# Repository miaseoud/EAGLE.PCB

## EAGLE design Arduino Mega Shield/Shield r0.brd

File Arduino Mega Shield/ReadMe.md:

# Arduino Mega Shield IRC'15 autonomous robot
The organization of shield is based on the needs 
of each connected device: (PWM, Servo, Analog,....)
+ the order of pins to use uni-directional cables

## Arduino Mega Shield autonomous robot supporting:
* 2x QTR 8 IR Analog sensor array
* 4x Servo Motors, signal supplied from Arduino and power supplied exnternally
* 1x ULN293 Motor Driver (PWM)
* 1x Motor Driver Module (PWM)
* 4x Digital Light Finder sensors
* 4x Digital IR sensors
* 3x Ultrasonic sensors

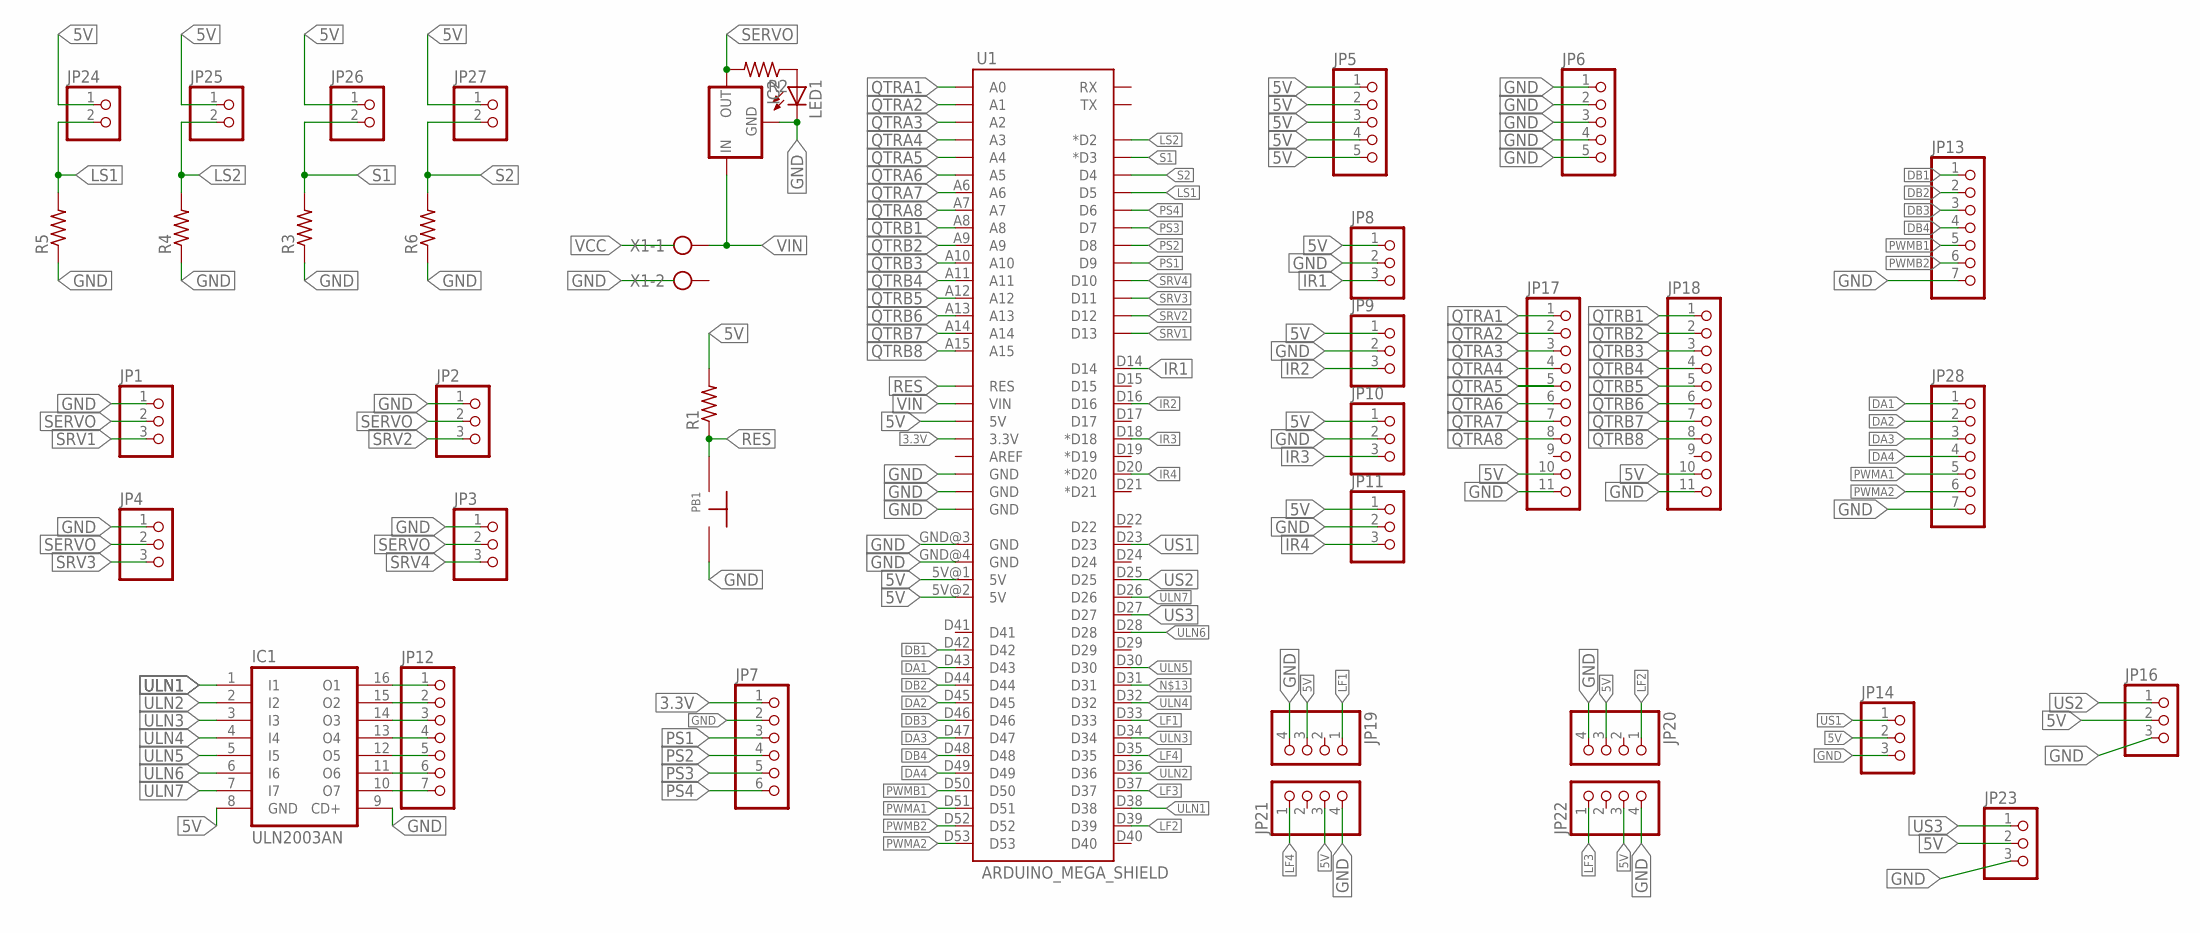
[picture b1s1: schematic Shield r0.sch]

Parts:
IC1: ULN2003AN; DIL16
IC2: 78XXS
JP1, JP2, JP3, JP4, JP8, JP9, JP10, JP11, JP14, JP16, JP23: PINHD-1X3; 1X03
JP5, JP6: PINHD-1X5; 1X05
JP7: PINHD-1X6; 1X06
JP12, JP13, JP28: PINHD-1X7; 1X07
JP17, JP18: PINHD-1X11; 1X11
JP19, JP20, JP21, JP22: PINHD-1X4; 1X04
JP24, JP25, JP26, JP27: PINHD-1X2; 1X02
LED1: LED5MM
PB1: PUSH; PUSHBUTTON
R1, R2, R3, R4, R5, R6: R-US_0207/10; 0207/10
U1: ARDUINO_MEGA_SHIELD
X1: AK500/2-H

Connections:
3.3V: JP7.1, U1.3.3V
5V: IC1.8 (GND), JP5.1, JP5.2, JP5.3, JP5.4, JP5.5, JP8.1, JP9.1, JP10.1, JP11.1, JP14.2, JP16.2, JP17.10, JP18.10, JP19.3, JP20.3, JP21.3, JP22.3, JP23.2, JP24.1, JP25.1, JP26.1, JP27.1, R1.2, U1.5V@0 (5V), U1.5V@1 (5V), U1.5V@2 (5V)
DA1: JP28.1, U1.D43
DA2: JP28.2, U1.D45
DA3: JP28.3, U1.D47
DA4: JP28.4, U1.D49
DB1: JP13.1, U1.D42
DB2: JP13.2, U1.D44
DB3: JP13.3, U1.D46
DB4: JP13.4, U1.D48
GND: IC1.9 (CD+), IC2.GND, JP1.1, JP2.1, JP3.1, JP4.1, JP6.1, JP6.2, JP6.3, JP6.4, JP6.5, JP7.2, JP8.2, JP9.2, JP10.2, JP11.2, JP13.7, JP14.3, JP16.3, JP17.11, JP18.11, JP19.4, JP20.4, JP21.4, JP22.4, JP23.3, JP28.7, LED1.K (C), PB1.P$2 (3), R3.1, R4.1, R5.1, R6.1, U1.GND@0 (GND), U1.GND@1 (GND), U1.GND@2 (GND), U1.GND@3 (GND), U1.GND@4 (GND)
IR1: JP8.3, U1.D14
IR2: JP9.3, U1.D16
IR3: JP10.3, U1.D18 (*D18)
IR4: JP11.3, U1.D20 (*D20)
LF1: JP19.1, U1.D33
LF2: JP20.1, U1.D39
LF3: JP22.1, U1.D37
LF4: JP21.1, U1.D35
LS1: JP24.2, R5.2, U1.D5
LS2: JP25.2, R4.2, U1.D2 (*D2)
unnamed: LED1.A, R2.1
unnamed: IC1.16 (O1), JP12.1
unnamed: IC1.15 (O2), JP12.2
unnamed: IC1.14 (O3), JP12.3
unnamed: IC1.13 (O4), JP12.4
unnamed: IC1.12 (O5), JP12.5
unnamed: IC1.11 (O6), JP12.6
unnamed: IC1.10 (O7), JP12.7
PS1: JP7.3, U1.D9
PS2: JP7.4, U1.D8
PS3: JP7.5, U1.D7
PS4: JP7.6, U1.D6
PWMA1: JP28.5, U1.D51
PWMA2: JP28.6, U1.D53
PWMB1: JP13.5, U1.D50
PWMB2: JP13.6, U1.D52
QTRA1: JP17.1, U1.A0
QTRA2: JP17.2, U1.A1
QTRA3: JP17.3, U1.A2
QTRA4: JP17.4, U1.A3
QTRA5: JP17.5, U1.A4
QTRA6: JP17.6, U1.A5
QTRA7: JP17.7, U1.A6
QTRA8: JP17.8, U1.A7
QTRB1: JP18.1, U1.A8
QTRB2: JP18.2, U1.A9
QTRB3: JP18.3, U1.A10
QTRB4: JP18.4, U1.A11
QTRB5: JP18.5, U1.A12
QTRB6: JP18.6, U1.A13
QTRB7: JP18.7, U1.A14
QTRB8: JP18.8, U1.A15
RES: PB1.P$1 (2), R1.1, U1.RES
S1: JP26.2, R3.2, U1.D3 (*D3)
S2: JP27.2, R6.2, U1.D4
SERVO: IC2.OUT, JP1.2, JP2.2, JP3.2, JP4.2, R2.2
SRV1: JP1.3, U1.D13
SRV2: JP2.3, U1.D12
SRV3: JP4.3, U1.D11
SRV4: JP3.3, U1.D10
ULN1: IC1.1 (I1), U1.D38
ULN2: IC1.2 (I2), U1.D36
ULN3: IC1.3 (I3), U1.D34
ULN4: IC1.4 (I4), U1.D32
ULN5: IC1.5 (I5), U1.D30
ULN6: IC1.6 (I6), U1.D28
ULN7: IC1.7 (I7), U1.D26
US1: JP14.1, U1.D23
US2: JP16.1, U1.D25
US3: JP23.1, U1.D27
VIN: IC2.IN, U1.VIN, X1.1

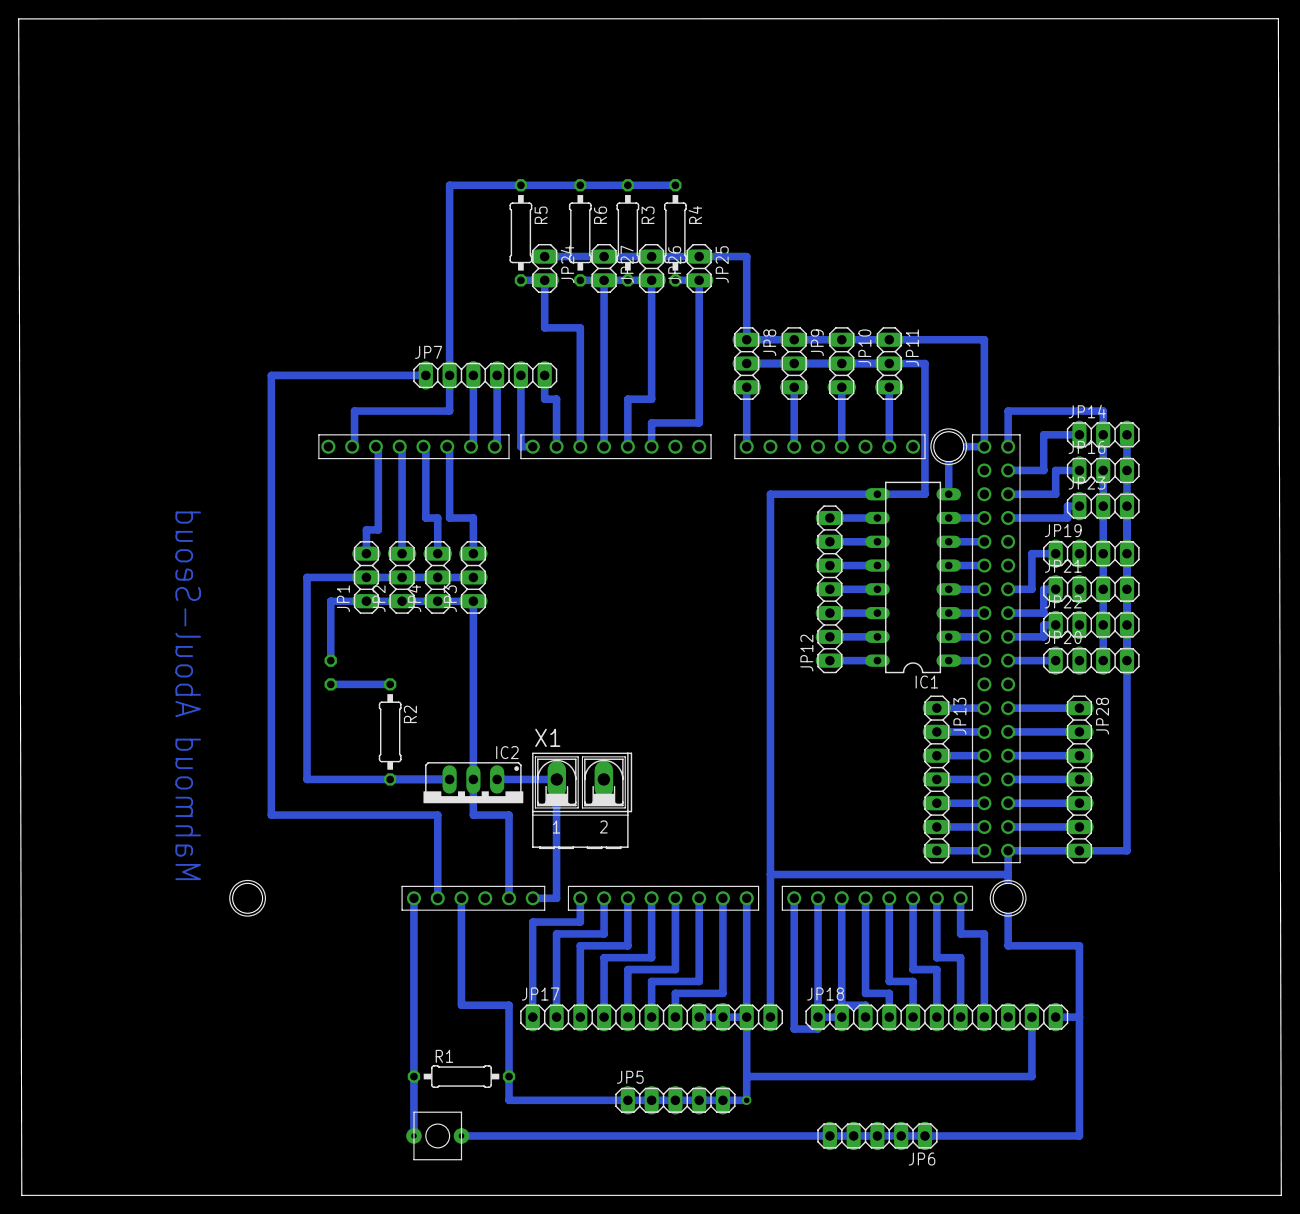
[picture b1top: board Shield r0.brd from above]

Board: 2 copper layers, 134.9 x 125.8 mm, 39 parts (1 on the bottom side), 72 nets.

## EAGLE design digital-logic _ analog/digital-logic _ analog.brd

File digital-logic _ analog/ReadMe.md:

# Off-shelf components robot
PCB for robot moving thorugh a maze using sensor,
but without the use of any microcontroller. Just relying 
on truth tables driving input for ULN293 motor driver.

IC connected on board:
Digital logic ICs: AND, OR, NOT
2x Op-amps
1x Counter 74190
1x MUX 74157
1x Timer IC 555
1x ULN293 motor driver
LEDs and Switches
2x digital sensors
1x analog sensor

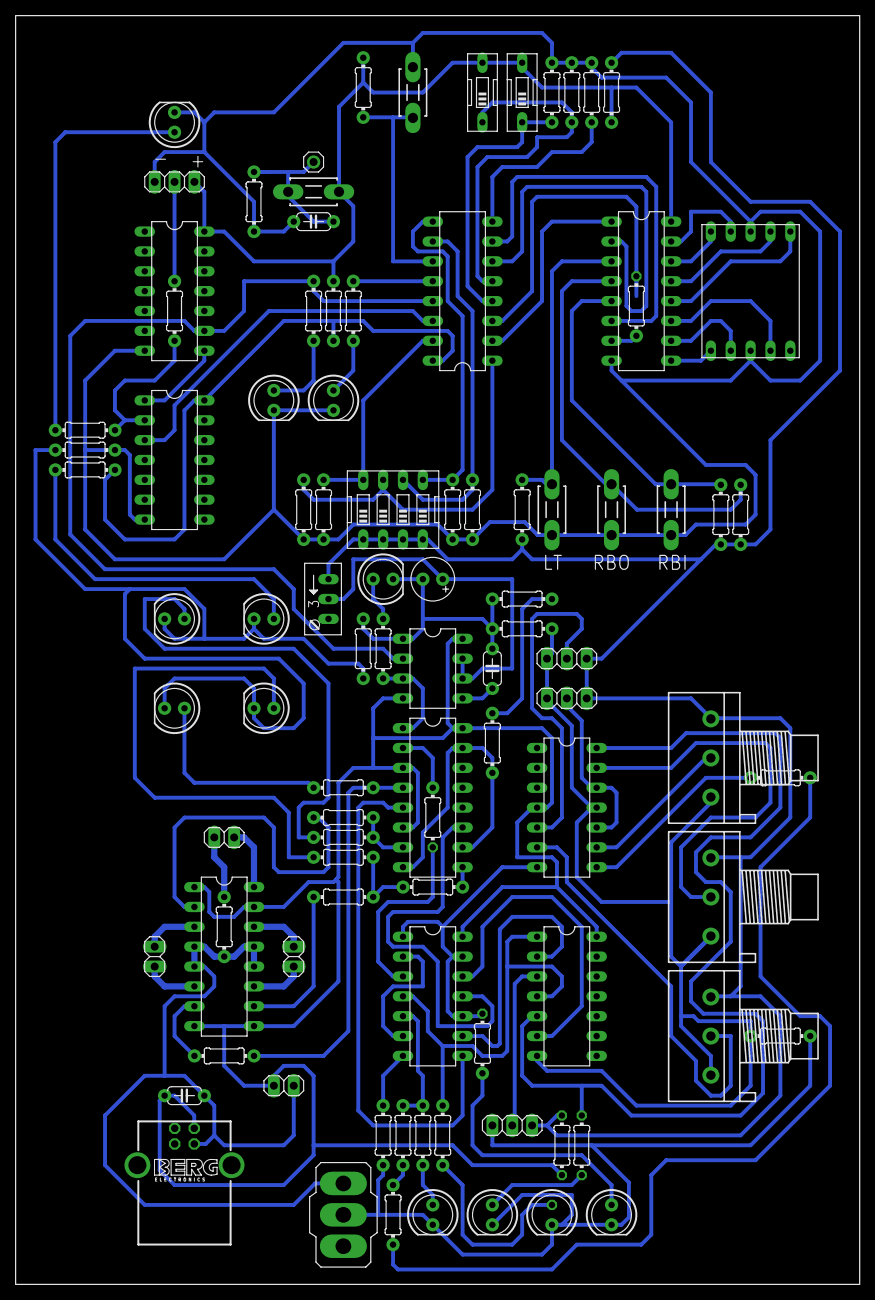
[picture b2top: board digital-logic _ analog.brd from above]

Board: 2 copper layers, 107.9 x 162.2 mm, 95 parts (0 on the bottom side), 68 nets.

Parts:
BLACK: 1X03
C1: 10nF; C050-024X044
C2, C3: 100nF; C050-024X044
C4: 1uF; E2,5-6
DIS1: HD-H103; HDSP-M
FLAME: 1X03
IC1: L293D; DIL16
IC2: LM324N; DIL14
IC3, IC9: 74LS32N; DIL14
IC4: 74ALS04N; DIL14
IC5: 74LS157N; DIL16
IC6: 74190N; DIL16
IC7: NE555; DIL-08
IC8: 74LS48N; DIL16
IC10: 74LS04N; DIL14
IR: 1X03
JP2, JP3, JP4, JP5: 1X02
JP7: 1X01
LED1, LED2, LED3, LED4, LED5, LED6, LED7, LED8, LED9, LED10, LED11, LED12: LED5MM
R1, R2, R3: 3RP/1610N
R4, R5, R6, R7, R8, R9, R10, R11, R13, R14, R15, R16, R17, R18, R19, R20, R21, R22, R23, R24, R25, R26, R49: 0204/7
R27, R28, R29, R30, R31, R32, R33, R34, R35, R36, R37, R38, R39, R40, R41, R42, R43, R44, R45, R46, R47, R48: 0; 0204/7
R50: RJ9W
S1: 320-916
S5: DTS-3; DTS-3@1
SHARP: 1X03
SW1: EDG-04
SW2, SW3, SW4, SW7: DTS-3; DTS-3@1
SW5, SW6: EDG-01
X1: PN61729-S

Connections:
BLACK: BLACK.2, IC9.2, R13.2, R36.1, R36.2
CLK: IC6.14, IC9.3
DIS: C4.+, IC7.6, IC7.7, R50.S
FLAME: IC2.7, IC3.1, IC3.10, IC3.13, R11.2
FRONT: IC3.4, IC4.1, IC4.4, R10.2
FRONT': IC4.3, IR.2
GND: BLACK.1, C1.2, C2.1, C3.2, C4.-, DIS1.3, DIS1.8, FLAME.1, IC1.4, IC1.5, IC1.12, IC1.13, IC2.11, IC3.7, IC4.7, IC5.8, IC5.10, IC5.15, IC6.8, IC7.1, IC8.8, IC9.7, IC10.7, IR.3, JP2.1, JP3.2, LED1.K, LED2.K, LED3.K, LED4.K, LED5.K, LED6.K, LED7.K, LED8.K, LED9.K, LED10.K, LED11.K, LED12.K, R1.1, R2.1, R3.1, R15.1, R16.1, R17.1, R18.1, R23.2, R24.2, R26.1, R28.1, R28.2, R33.1, R33.2, R34.1, R34.2, R37.1, R37.2, R39.1, R39.2, R40.1, R40.2, R42.1, R42.2, R43.1, R43.2, R44.1, R44.2, S1.1, S1.2, SHARP.1, SW2.2, SW3.2, SW4.2, SW7.2, X1.4
HAMADA: IC1.11, JP5.2
L1: IC1.2, IC5.7, R6.2, R30.1, R30.2
L2: IC1.7, IC5.4, R7.2, R45.1, R45.2
LOGIC_L1: IC3.8, IC5.5
LOGIC_L2: IC3.3, IC5.2, R35.1, R35.2
LOGIC_R2: IC3.11, IC5.11
MAX: IC2.14, IC4.5, R9.2
MIN: IC2.8, IC3.5, R8.2, R46.1, R46.2, R47.1, R47.2, R48.1, R48.2
MOTOR_SUPPLY: IC1.16, JP2.2
unnamed: FLAME.2, IC2.5
unnamed: IC2.10, IC2.12, SHARP.2
unnamed: LED5.A, R4.1
unnamed: IC3.12, IC4.6
unnamed: IC2.6, R1.2
unnamed: C1.1, IC7.5
unnamed: LED6.A, R5.1
unnamed: IC3.2, IC3.6
unnamed: LED7.A, R6.1
unnamed: LED8.A, R7.1
unnamed: IC2.9, R2.2
unnamed: IC1.14, JP5.1
unnamed: IC1.3, JP4.2
unnamed: IC1.6, JP4.1
unnamed: LED12.A, R49.1
unnamed: IC2.13, R3.2
unnamed: LED1.A, R8.1
unnamed: LED11.A, R13.1
unnamed: IC3.9, IC4.2
unnamed: LED2.A, R9.1
unnamed: LED3.A, R10.1
unnamed: LED4.A, R11.1
unnamed: IC9.1, IC10.8
unnamed: IC6.3, IC8.7, R27.1, R27.2
unnamed: IC6.2, IC8.1
unnamed: IC6.6, IC8.2
unnamed: IC6.7, IC8.6
unnamed: IC6.15, R15.2, SW1.8
unnamed: IC6.1, R16.2, SW1.7
unnamed: IC6.10, R17.2, SW1.6
unnamed: IC6.9, R18.2, SW1.5
unnamed: IC6.4, R23.1, SW5.1
unnamed: IC6.5, R24.1, SW6.1
unnamed: IC6.11, R25.1, SW7.1
unnamed: IC8.4, R20.1, SW2.1
unnamed: IC8.5, R21.1, SW3.1
unnamed: IC8.3, R22.1, SW4.1
unnamed: DIS1.7, IC8.13
unnamed: DIS1.6, IC8.12
unnamed: DIS1.4, IC8.11
unnamed: DIS1.2, IC8.10
unnamed: DIS1.1, IC8.9
unnamed: DIS1.9, IC8.15
unnamed: DIS1.10, IC8.14
unnamed: IC6.12, R14.2
unnamed: LED9.A, R19.1
unnamed: LED10.A, R14.1
unnamed: C3.1, JP7.1, R26.2, S5.2
R2: IC1.10, IC5.9, R5.2, R31.1, R31.2, R32.1, R32.2
RCO: IC6.13, IC7.2, IC10.9, R19.2
SENSE: IC5.1, IC7.3, R49.2
VCC: BLACK.3, C2.2, FLAME.3, IC1.1, IC1.8, IC1.9, IC1.15, IC2.4, IC3.14, IC4.14, IC5.3, IC5.6, IC5.16, IC6.16, IC7.4, IC7.8, IC8.16, IC9.14, IC10.14, IR.1, JP3.1, R1.3, R2.3, R3.3, R4.2, R20.2, R21.2, R22.2, R25.2, R29.1, R29.2, R38.1, R38.2, R41.1, R41.2, R50.E, S5.1, SHARP.3, SW1.1, SW1.2, SW1.3, SW1.4, SW5.2, SW6.2, X1.1

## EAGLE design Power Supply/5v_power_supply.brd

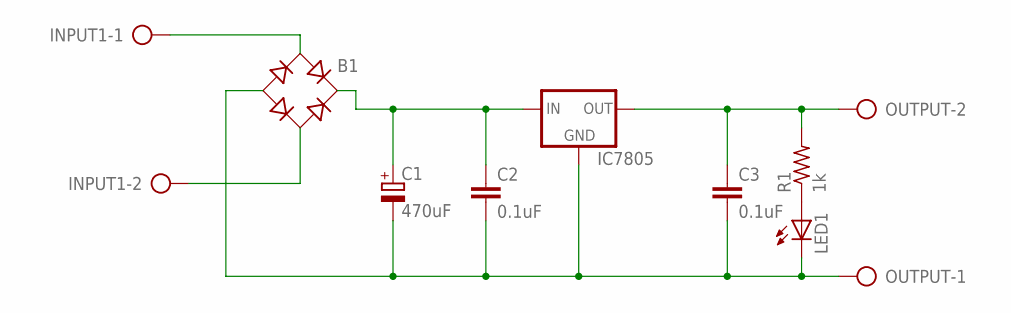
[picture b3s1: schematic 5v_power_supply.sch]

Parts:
B1: RB1A
C1: 470uF; B45181B
C2, C3: 0.1uF; C050-025X075
IC7805: 78XXS
INPUT1: AK500/2-H
LED1: LED5MM
OUTPUT: AK500/2-H
R1: 1k; 0207/10

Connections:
unnamed: B1.AC1, INPUT1.1
unnamed: B1.AC2, INPUT1.2
unnamed: B1.+, C1.+, C2.1, IC7805.IN
unnamed: B1.-, C1.-, C2.2, C3.2, IC7805.GND, LED1.K (C), OUTPUT.1
unnamed: C3.1, IC7805.OUT, OUTPUT.2, R1.2
unnamed: LED1.A, R1.1

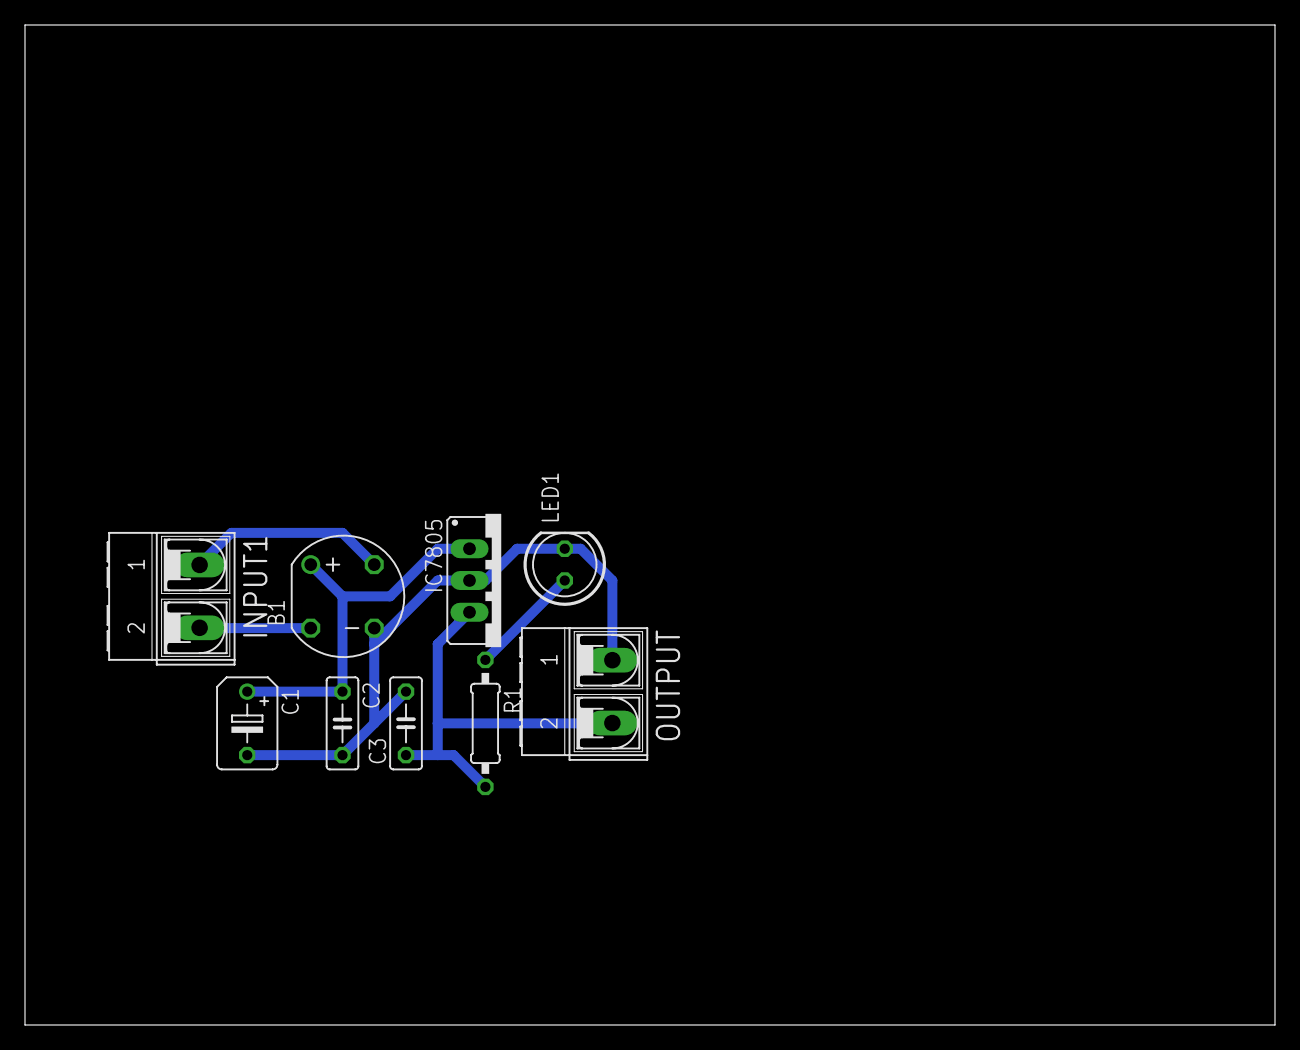
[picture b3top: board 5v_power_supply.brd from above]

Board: 2 copper layers, 100.0 x 80.0 mm, 9 parts (0 on the bottom side), 6 nets.

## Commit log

2017-11-06 3 PCBs 1st commit
2017-11-06 adjusting names
2017-11-06 List adjust
